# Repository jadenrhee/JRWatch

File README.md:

# JRWatch

A smartwatch designed from scratch, board included. 36 mm across and 4
layers, with an nRF52840 for Bluetooth, an nPM1300 handling charging and
the power rails, a BMI270 for motion, and a Sharp memory-in-pixel LCD
that holds a static image on about 12 µW. Firmware runs on Zephyr.

Most of the design work went into idle current, meaning what it draws
while sitting on a wrist doing nothing.

<p align="center"><sub>Front copper on the left, back on the right. 36 x 36 mm, 4 layers.</sub></p>

| | |
|---|---|
| Sleep current | ~15 µA, or ~26 µA while advertising over Bluetooth (1.5 s interval, not connected) |
| Battery life | ~4 months connected to a phone all day, ~8 months mostly idle, on a 150 mAh cell |
| Firmware | Zephyr v4.1.0, 232 KiB flash / 40 KiB RAM |

These are calculated from datasheet typicals, not measured on hardware.
The full itemization is in the
[verification report](docs/verification-report.md). Part choices are in
the [design rationale](docs/design-rationale.md).

## Architecture

```mermaid
flowchart LR
  USB["USB-C"]
  BAT["LiPo 150 mAh<br/>+ 10k NTC"]
  PMIC["nPM1300<br/>charger, 2 bucks,<br/>2 load switches"]
  MCU["nRF52840<br/>MDBT50Q-1MV2"]
  DISP["Sharp LS013B7DH03<br/>128 x 128 MIP"]
  IMU["Bosch BMI270"]

  USB -->|VBUS| PMIC
  BAT -->|VBAT| PMIC
  PMIC -->|3V0 always-on| MCU
  PMIC -->|VDD_DISP via LSW1| DISP
  PMIC -->|VDD_IMU via LSW2| IMU

  MCU -.->|I2C 0x6b| PMIC
  MCU -.->|SPI2| DISP
  MCU -.->|SPI1| IMU
```

Solid lines are power, dashed are data. The display and IMU sit behind
load switches inside the PMIC. In armed sleep they draw about 4 µA and
6 µA. Ship mode disconnects the battery entirely and the whole watch
drops to 370 nA, low enough that cell self-discharge dominates. Full net
list is in [`hardware/skidl/jrwatch.py`](hardware/skidl/jrwatch.py).

## Status

Not yet fabricated. A review before ordering turned up a problem with
the display connector, and both halves of it trace to one cause. The
panel's ribbon exits the center and has to fold 180 degrees back
underneath. That fold leaves roughly a 9 mm window where the connector
can sit, and mine was outside it. The fold also inverts the contact
face, which reverses the pin order, and I had the pins running straight
through.

The pin order is corrected in the schematic. Repositioning the connector
is a layout change and hasn't landed yet, so ordering is blocked.
Written up as D-025 in the [decision log](docs/decision-log.md).

## Firmware

An out-of-tree Zephyr board port with devicetree, Kconfig, and board
files. Three power modes cover active, armed sleep, and off. The display
redraws only when its content changes, and the IMU wakes the SoC on
motion. BLE reports battery level and step count
([protocol](docs/protocol.md)).

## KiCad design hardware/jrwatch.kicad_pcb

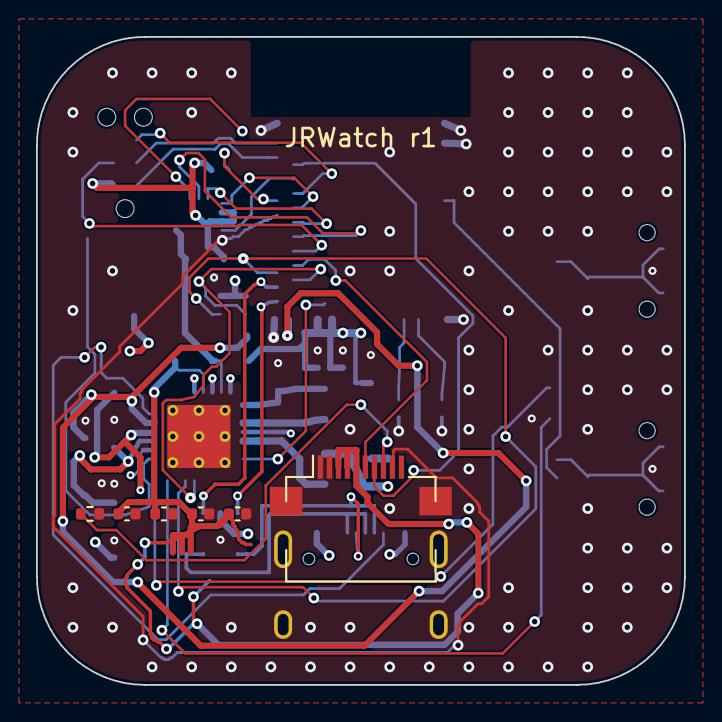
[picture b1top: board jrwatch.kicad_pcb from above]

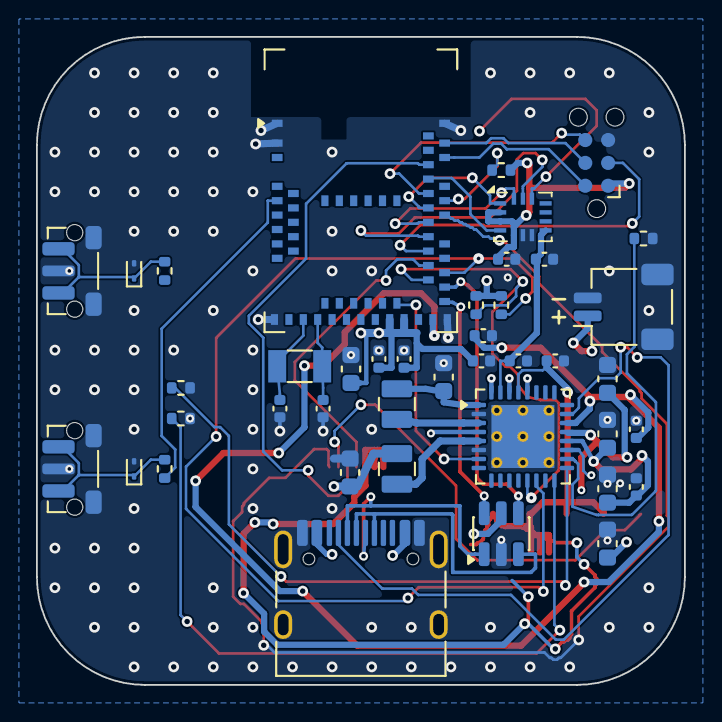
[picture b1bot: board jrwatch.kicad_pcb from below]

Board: 4 copper layers, 36.0 x 36.0 mm, 47 parts (41 on the bottom side), 43 nets.

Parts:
C1, C2, C5, C7, C8, C12: 10uF; C_0603_1608Metric
C3: 2.2uF; C_0603_1608Metric
C4, C11, C13, C14, C15, C18, C19, C21, C23: 100nF; C_0402_1005Metric
C6, C9, C10, C20, C22: 1uF; C_0402_1005Metric
C16, C17: 12pF; C_0402_1005Metric
D1: ESD9B5.0; D_SOD-923
D2: ESD9B3.3; D_SOD-923
J1: TYPE-C-31-M-12; USB_C_Receptacle_HRO_TYPE-C-31-M-12
J2: FH12A-10S-0.5SH; Hirose_FH12-10S-0.5SH_1x10-1MP_P0.50mm_Horizontal
J3: SM02B-SRSS-TB; JST_SH_SM02B-SRSS-TB_1x02-1MP_P1.00mm_Horizontal
J4: TC2030-IDC-NL; Tag-Connect_TC2030-IDC-NL_2x03_P1.27mm_Vertical
L1, L2: 2.2uH; L_Murata_DFE201612E_2016
R1: 47k; R_0402_1005Metric
R2: 150k; R_0402_1005Metric
R3, R4: 4.7k; R_0402_1005Metric
R5, R6: 100k; R_0402_1005Metric
R7, R8: 100R; R_0402_1005Metric
RT1: 10k NTC; R_0402_1005Metric
SW1: PWR/SHIP; SW_Push_1P1T-MP_NO_Horizontal_Alps_SKRTLAE010
SW2: USER; SW_Push_1P1T-MP_NO_Horizontal_Alps_SKRTLAE010
U1: MDBT50Q-1MV2; Raytac_MDBT50Q
U2: nPM1300-QEAA-R7; VQFN-32-1EP_5x5mm_P0.5mm_EP3.5x3.5mm_ThermalVias
U3: BMI270; Bosch_LGA-14_3x2.5mm_P0.5mm
U4: USBLC6-2SC6; SOT-23-6
Y1: 32.768kHz; Crystal_SMD_3215-2Pin_3.2x1.5mm

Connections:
1V8_AUX: C7.1, L1.2, U2.1
3V0: C8.1, C11.1, C12.1, C13.1, C14.1, C19.1, J4.1, L2.2, R3.2, R4.2, R5.2, U1.28, U1.30, U2.12, U2.28, U2.30, U2.32, U3.2, U3.3, U3.5
BTN1_PAD: D1.1, R7.2, SW1.1
BTN2: R8.1, U1.6
BTN2_PAD: D2.1, R8.2, SW2.1
CC1: J1.A5, U2.23
CC2: J1.B5, U2.24
DISP_CS: J2.8, R6.1, U1.39
DISP_MOSI: J2.9, U1.44
DISP_ON: J2.6, U1.38
DISP_SCK: J2.10, U1.41
EXTCOMIN: J2.7, U1.50
GND: C1.2, C2.2, C3.2, C4.2, C5.2, C6.2, C7.2, C8.2, C9.2, C10.2, C11.2, C12.2, C13.2, C14.2, C15.2, C16.2, C17.2, C18.2, C19.2, C20.2, C21.2, C22.2, C23.2, D1.2, D2.2, J1.A1, J1.A12, J1.B1, J1.B12, J1.SH, J2.1, J2.2, J2.MP, J3.2, J3.MP, J4.5, R1.2, R2.2, R6.2, RT1.2, SW1.2, SW1.MP, SW2.2, SW2.MP, U1.1, U1.2, U1.15, U1.33, U1.55, U2.2, U2.6, U2.33, U3.6, U3.7, U4.2
I2C_SCL: R4.1, U1.37, U2.14
I2C_SDA: R3.1, U1.36, U2.13
IMU_CS: R5.1, U1.46, U3.12
IMU_INT1: U1.49, U3.4
IMU_MISO: U1.45, U3.1
IMU_MOSI: U1.43, U3.14
IMU_SCK: U1.42, U3.13
unnamed: L1.1, U2.3
unnamed: R1.1, U2.17
unnamed: L2.1, U2.5
unnamed: R2.1, U2.16
NTC: RT1.1, U2.18
PMIC_INT: U1.29, U2.7
SHPHLD: R7.1, U2.15
SWDCLK: J4.4, U1.53
SWDIO: J4.2, U1.51
SWO: J4.6, U1.47
USB_DM: U1.34, U4.6
USB_DM_CONN: J1.A7, J1.B7, U4.1
USB_DP: U1.35, U4.4
USB_DP_CONN: J1.A6, J1.B6, U4.3
VBAT: C1.1, J3.1, U2.19
VBUS_OUT: C6.1, C15.1, U1.32, U2.22
VBUS_USB: C5.1, J1.A4, J1.A9, J1.B4, J1.B9, U2.21, U4.5
VDD_DISP: C9.1, C20.1, C21.1, C22.1, C23.1, J2.3, J2.4, J2.5, U2.29
VDD_IMU: C10.1, C18.1, U2.31, U3.8
VSYS: C2.1, C3.1, C4.1, U2.4, U2.20
XL1: C16.1, U1.17, Y1.2
XL2: C17.1, U1.18, Y1.1
nRESET: J4.3, U1.40

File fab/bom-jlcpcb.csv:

Comment,Designator,Footprint,LCSC
10uF,"C1,C12,C2,C5,C7,C8",C_0603_1608Metric,C19702
1uF,"C10,C20,C22,C6,C9",C_0402_1005Metric,C52923
100nF,"C11,C13,C14,C15,C18,C19,C21,C23,C4",C_0402_1005Metric,C1525
12pF,"C16,C17",C_0402_1005Metric,C1547
2.2uF,C3,C_0603_1608Metric,C23630
ESD9B5.0,D1,D_SOD-923,C3008065
ESD9B3.3,D2,D_SOD-923,C96512
TYPE-C-31-M-12,J1,USB_C_Receptacle_HRO_TYPE-C-31-M-12,C165948
FH12A-10S-0.5SH [HAND-PLACE],J2,Hirose_FH12-10S-0.5SH_1x10-1MP_P0.50mm_Horizontal,C5139870
SM02B-SRSS-TB,J3,JST_SH_SM02B-SRSS-TB_1x02-1MP_P1.00mm_Horizontal,C160402
2.2uH,"L1,L2",L_Murata_DFE201612E_2016,C337893
47k,R1,R_0402_1005Metric,C25792
150k,R2,R_0402_1005Metric,C25755
4.7k,"R3,R4",R_0402_1005Metric,C25900
100k,"R5,R6",R_0402_1005Metric,C25741
100R,"R7,R8",R_0402_1005Metric,C25076
10k NTC,RT1,R_0402_1005Metric,C77131
PWR/SHIP,SW1,SW_Push_1P1T-MP_NO_Horizontal_Alps_SKRTLAE010,C110293
USER,SW2,SW_Push_1P1T-MP_NO_Horizontal_Alps_SKRTLAE010,C110293
"MDBT50Q-1MV2 [HAND-PLACE: DigiKey, LCSC OOS at design time]",U1,Raytac_MDBT50Q,C5118826
"nPM1300-QEAA-R7 [HAND-PLACE: DigiKey, LCSC OOS at design time]",U2,VQFN-32-1EP_5x5mm_P0.5mm_EP3.5x3.5mm_ThermalVias,C7501206
BMI270,U3,Bosch_LGA-14_3x2.5mm_P0.5mm,C2836813
USBLC6-2SC6,U4,SOT-23-6,C7519
32.768kHz,Y1,Crystal_SMD_3215-2Pin_3.2x1.5mm,C32346

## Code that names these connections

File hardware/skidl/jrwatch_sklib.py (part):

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            Pin(num='12',name='VDDIO',func=pin_types.PWRIN),
            Pin(num='13',name='SDA',func=pin_types.BIDIR),
            Pin(num='14',name='SCL',func=pin_types.INPUT),
            Pin(num='15',name='SHPHLD',func=pin_types.INPUT),
            Pin(num='16',name='VSET2',func=pin_types.INPUT),
            Pin(num='17',name='VSET1',func=pin_types.INPUT),
            Pin(num='18',name='NTC',func=pin_types.INPUT),
            Pin(num='19',name='VBAT',func=pin_types.PWRIN),
            Pin(num='20',name='VSYS',func=pin_types.PWROUT),
            Pin(num='21',name='VBUS',func=pin_types.PWRIN),
            Pin(num='22',name='VBUSOUT',func=pin_types.PWROUT),
            Pin(num='23',name='CC1',func=pin_types.BIDIR),
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            Pin(num='37',name='P0.13',func=pin_types.BIDIR),
            Pin(num='38',name='P0.16',func=pin_types.BIDIR),
            Pin(num='39',name='P0.15',func=pin_types.BIDIR),
            Pin(num='40',name='P0.18/nRESET',func=pin_types.BIDIR),
            Pin(num='41',name='P0.17',func=pin_types.BIDIR),
            Pin(num='42',name='P0.19',func=pin_types.BIDIR),
            Pin(num='43',name='P0.21',func=pin_types.BIDIR),
            Pin(num='44',name='P0.20',func=pin_types.BIDIR),
            Pin(num='45',name='P0.23',func=pin_types.BIDIR),
            Pin(num='46',name='P0.22',func=pin_types.BIDIR),
            Pin(num='47',name='P1.00/SWO',func=pin_types.BIDIR),
            Pin(num='48',name='P0.24',func=pin_types.BIDIR),
            Pin(num='49',name='P0.25',func=pin_types.BIDIR),
            Pin(num='50',name='P1.02',func=pin_types.BIDIR),
            Pin(num='51',name='SWDIO',func=pin_types.BIDIR),
            Pin(num='52',name='P0.09/NFC1',func=pin_types.BIDIR),
            Pin(num='53',name='SWDCLK',func=pin_types.INPUT),
            Pin(num='54',name='P0.10/NFC2',func=pin_types.BIDIR),
            Pin(num='55',name='GND',func=pin_types.PWRIN),
            Pin(num='56',name='P1.04',func=pin_types.BIDIR),
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            Pin(num='1',name='VTREF',func=pin_types.PWRIN),
            Pin(num='2',name='SWDIO',func=pin_types.BIDIR),
            Pin(num='3',name='nRESET',func=pin_types.BIDIR),
            Pin(num='4',name='SWDCLK',func=pin_types.BIDIR),
            Pin(num='5',name='GND',func=pin_types.PWRIN),
            Pin(num='6',name='SWO',func=pin_types.BIDIR)] }),
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            Pin(num='A1',name='GND',func=pin_types.PWRIN),
            Pin(num='A12',name='GND',func=pin_types.PWRIN),
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            Pin(num='4',name='VDD',func=pin_types.PWRIN),
            Pin(num='5',name='VDDA',func=pin_types.PWRIN),
            Pin(num='6',name='DISP',func=pin_types.INPUT),
            Pin(num='7',name='EXTCOMIN',func=pin_types.INPUT),
            Pin(num='8',name='SCS',func=pin_types.INPUT),
            Pin(num='9',name='SI',func=pin_types.INPUT),
            Pin(num='10',name='SCLK',func=pin_types.INPUT),
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            Pin(num='1',name='1',func=pin_types.PASSIVE),
            Pin(num='2',name='2',func=pin_types.PASSIVE),
            Pin(num='MP',name='MP',func=pin_types.PASSIVE)] }),
        Part(**{ 'name':'ESD9B5.0ST5G', 'dest':TEMPLATE, 'tool':SKIDL, 'aliases':Alias({'ESD9B5.0ST5G'}), 'ref_prefix':'D', 'fplist':None, 'footprint':'Diode_SMD:D_SOD-923', 'keywords':None, 'description':'Bidirectional ESD TVS, 5.0 V working (SHPHLD swings to VBAT)', 'datasheet':None, 'pins':[
            Pin(num='1',name='A1',func=pin_types.PASSIVE),
            Pin(num='2',name='A2',func=pin_types.PASSIVE)] }),
        Part(**{ 'name':'ESD9B3.3ST5G', 'dest':TEMPLATE, 'tool':SKIDL, 'aliases':Alias({'ESD9B3.3ST5G'}), 'ref_prefix':'D', 'fplist':None, 'footprint':'Diode_SMD:D_SOD-923', 'keywords':None, 'description':'Bidirectional ESD TVS, 3.3 V working (logic-level button line)', 'datasheet':None, 'pins':[
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
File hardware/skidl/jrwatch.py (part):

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  usb     - USB-C data pairs through USBLC6 ESD to the module
  imu     - BMI270 on its own SPI, INT1 motion wake
  display - Sharp MIP LCD via 10-pin FPC, gated rail
  controls- SW1 power (SHPHLD), SW2 user (GPIO wake), both ESD-protected
"""
import json
import os
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    r = res('4.7k')
    pull_net += r[1]
    v3v0 += r[2]
u2['GPIO0'] += pmic_int
u2['SHPHLD'] += shphld
for p in ('GPIO1', 'GPIO2', 'GPIO3', 'GPIO4', 'LED0', 'LED1', 'LED2'):
    u2[p] += NC
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u1[44] += disp_mosi                      # P0.20
u1[39] += disp_cs                        # P0.15
u1[38] += disp_on                        # P0.16
u1[50] += extcomin                       # P1.02 (LF pin, 1 Hz signal - allowed)
u1[6]  += btn2                           # P1.13 (LF pin, button - allowed)

# unused module pins
u1[31] += NC                             # DCCH - REG0 unused in normal-voltage mode
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j2[6] += disp_on                         # DISP
j2[5] += vdd_disp                        # VDDA
j2[4] += vdd_disp                        # VDD
j2[3] += vdd_disp                        # EXTMODE=H -> EXTCOMIN pin mode (Sharp Rmk 4-1)
j2[2] += gnd                             # VSS
j2[1] += gnd                             # VSSA
j2['MP'] += gnd
decouple(vdd_disp, '1uF', '100nF', '1uF', '100nF')   # VDD + VDDA pairs

# ================================================================= CONTROLS
# SW1: power button -> SHPHLD only (node swings to VBAT - never to an nRF pin, D-014)
sw1 = TACT_SIDE(ref='SW1', value='PWR/SHIP')
d1 = ESD_5V0(ref='D1', value='ESD9B5.0')
r_sw1 = res('100R')
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
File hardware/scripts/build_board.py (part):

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        # Courtyard envelopes (KiCad lib): 0402 = 1.92 x 1.12 mm, 0603 =
        # 2.96 x 1.52 mm, custom L = 3.16 x 2.2. Pitches below respect them.
        # west column x=86.3, 0603 rot-90, pitch 3.05
        sat('10uF', 'VBUS_USB',  86.3, 101.0, 90)      # VBUS pin (closest)
        sat('2.2uF', 'VSYS',     86.3, 104.05, 90)
        sat('10uF', 'VSYS',      86.3, 107.1, 90)      # VSYS pin
        sat('10uF', 'VBAT',      86.3, 110.15, 90)     # VBAT (battery is west anyway)
        sat('1uF', 'VBUS_OUT',   84.7, 103.8, 90)      # VBUSOUT (west of col)
        sat('100nF', 'VSYS',     84.7, 107.0, 90)       # PVDD 100n on west bank
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        sat('100nF', '3V0',      97.6, 99.9, 90, idx=1)     # VDD
        sat('100nF', '3V0',      99.0, 99.9, 90, idx=2)     # VDDH
        sat('10uF', '3V0',       100.55, 100.45, 90, idx=1)   # module bulk
        sat('100nF', 'VBUS_OUT', 93.2, 98.6, 0)             # module VBUS pin32 (96.0,97.7)
        # crystal load caps - row south of Y1 (XL pads at 103.2/102.4, 97.7);
        # XL2 stack west, XL1 stack east (matches crystal pin swap, no crossover)
        sat('18pF', 'XL2',       102.1, 102.65, 270)
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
